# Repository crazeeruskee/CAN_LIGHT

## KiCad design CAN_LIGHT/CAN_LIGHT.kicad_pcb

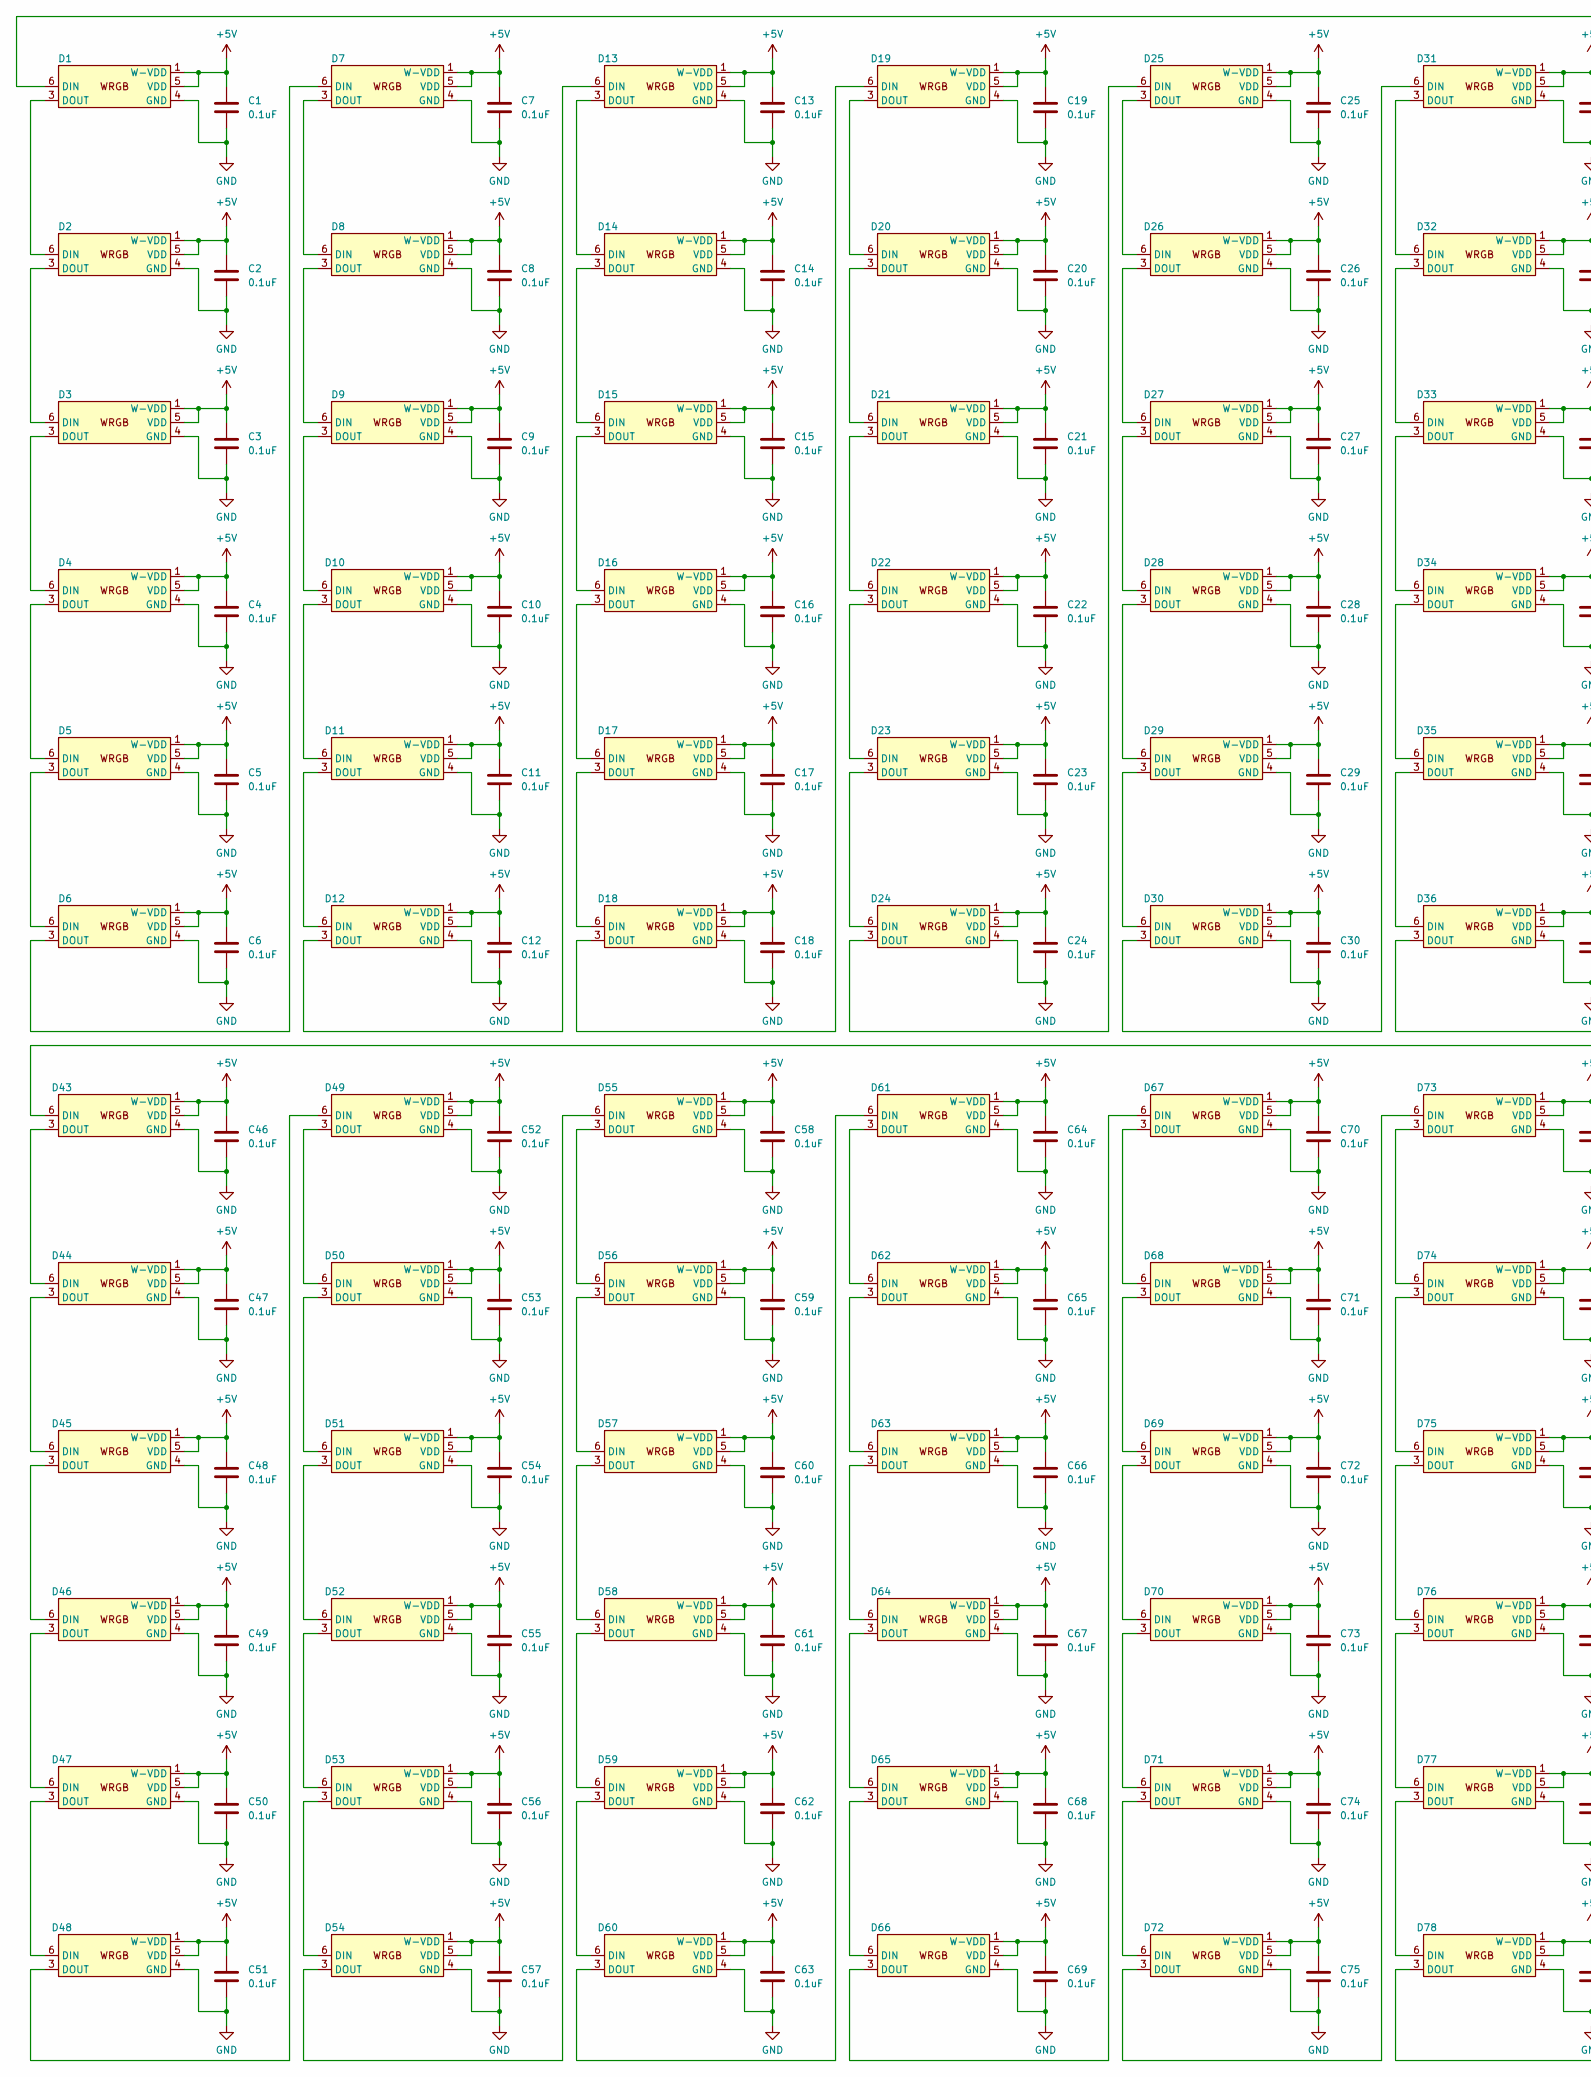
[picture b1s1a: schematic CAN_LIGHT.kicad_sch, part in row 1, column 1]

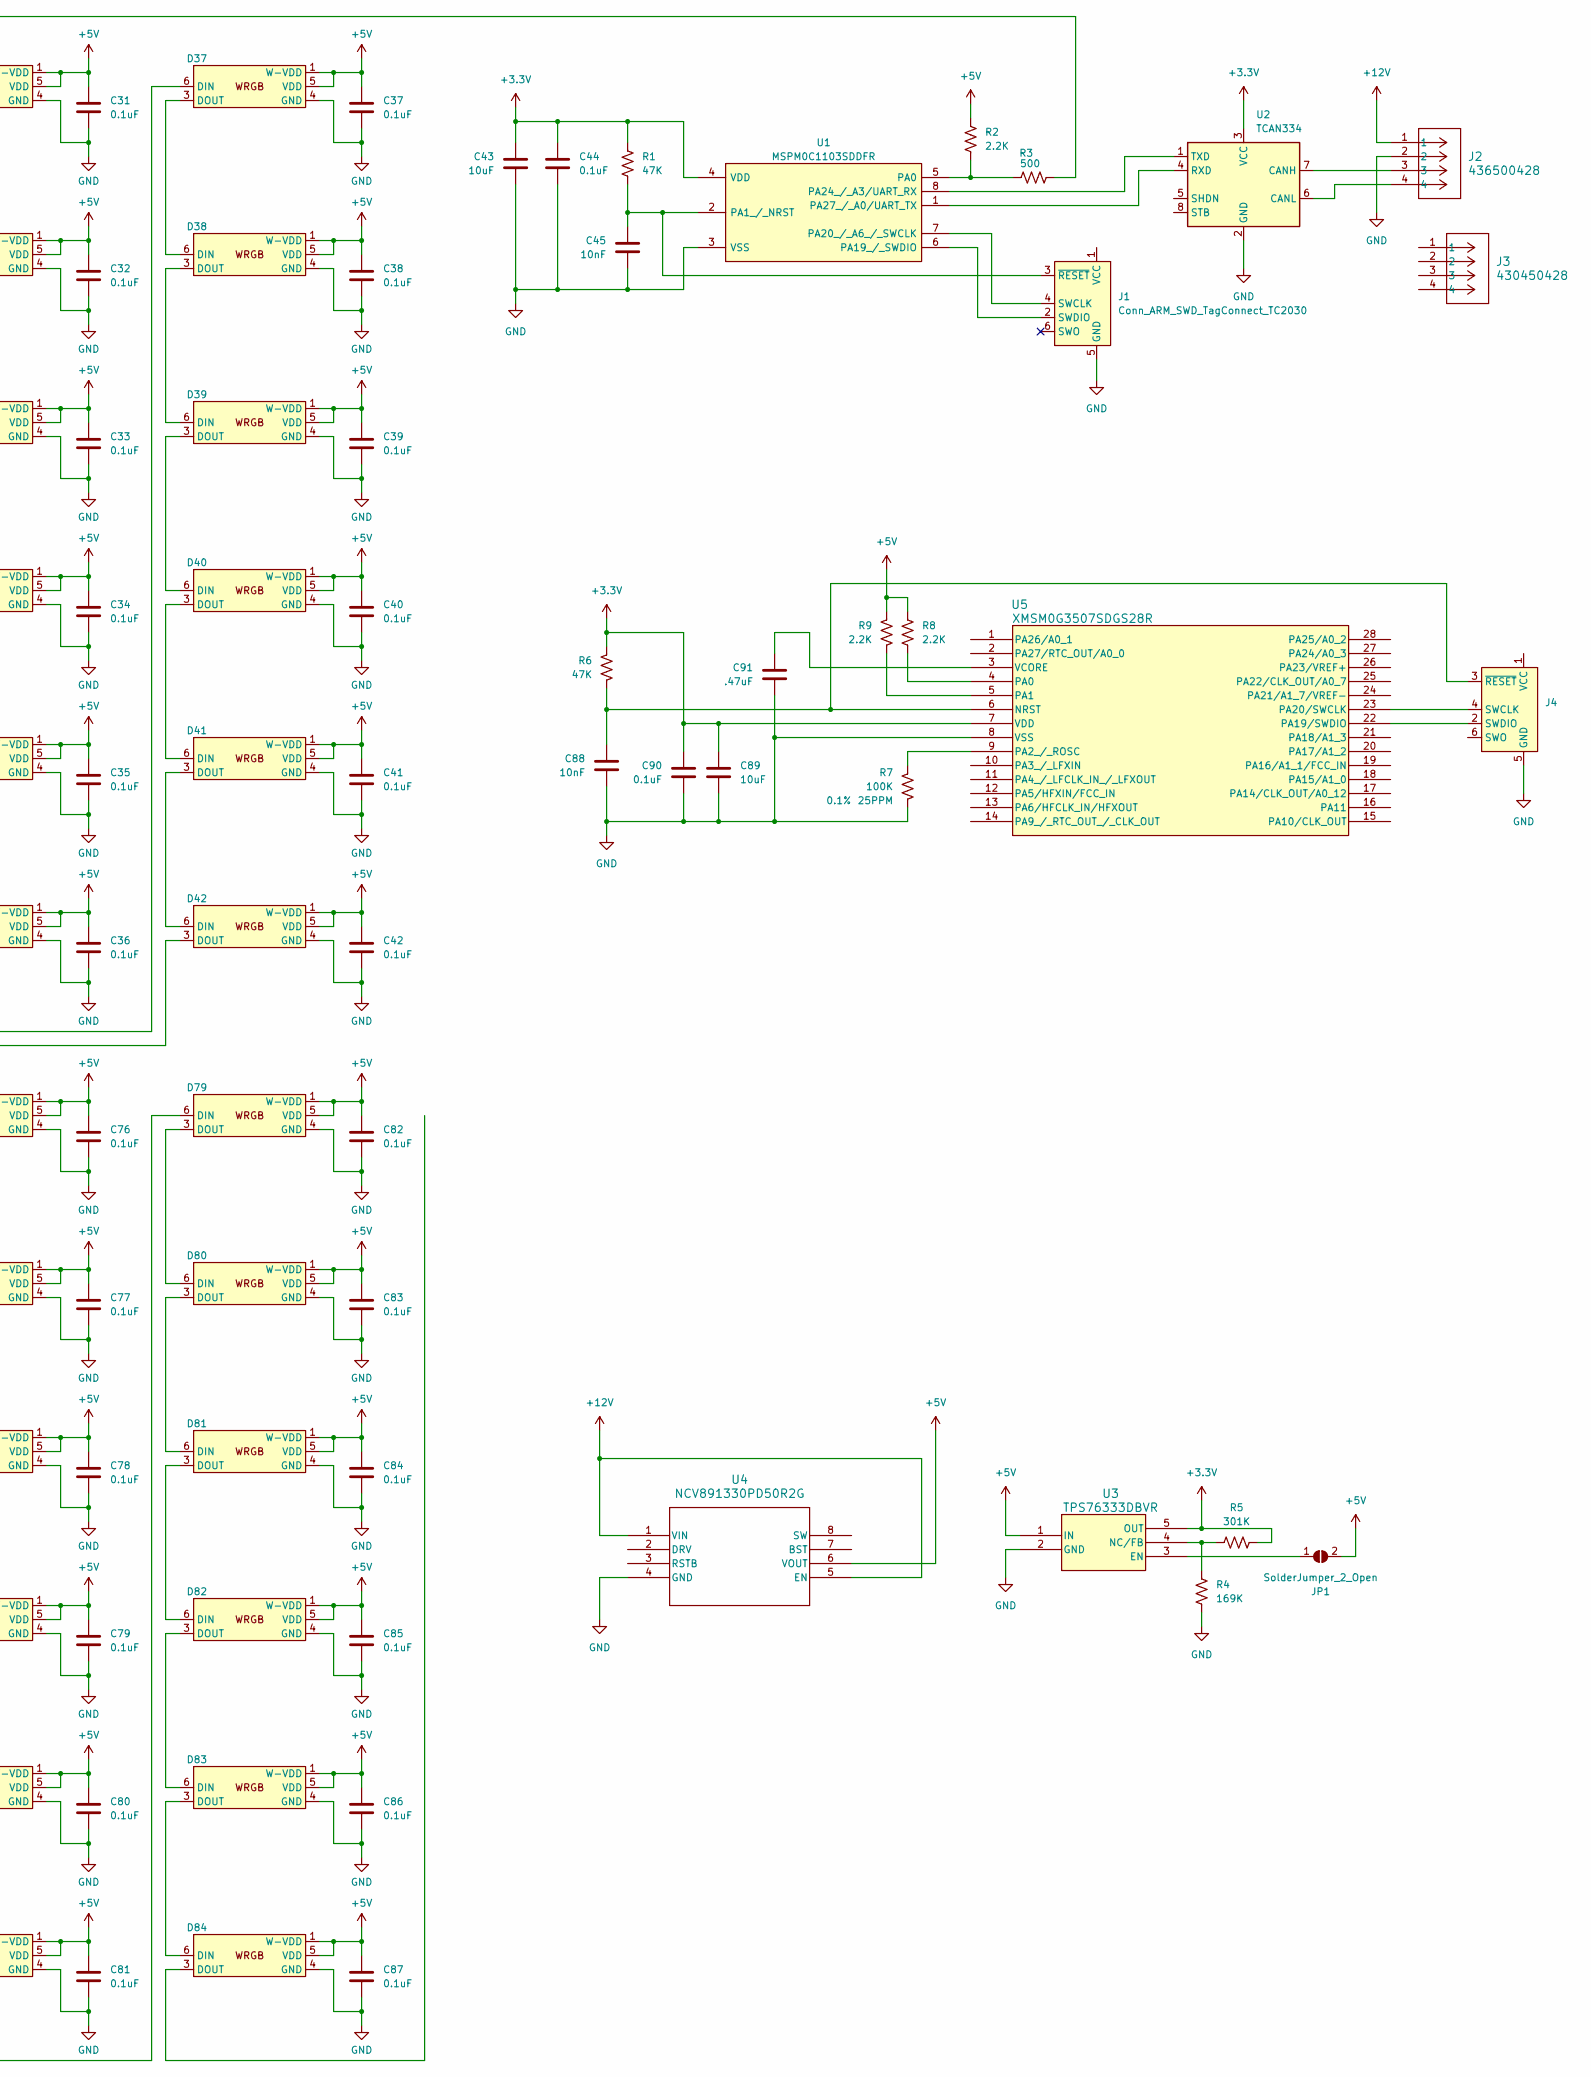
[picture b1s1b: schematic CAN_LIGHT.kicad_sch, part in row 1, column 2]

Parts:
C1, C2, C3, C4, C5, C6, C7, C8, C9, C10, C11, C12, C13, C14, C15, C16, C17, C18, C19, C20, C21, C22, C23, C24, C25, C26, C27, C28, C29, C30, C31, C32, C33, C34, C35, C36, C37, C38, C39, C40, C41, C42, C44, C46, C47, C48, C49, C50, C51, C52, C53, C54, C55, C56, C57, C58, C59, C60, C61, C62, C63, C64, C65, C66, C67, C68, C69, C70, C71, C72, C73, C74, C75, C76, C77, C78, C79, C80, C81, C82, C83, C84, C85, C86, C87, C90: 0.1uF; C_0603_1608Metric_Pad1.08x0.95mm_HandSolder
C43, C89: 10uF; C_0603_1608Metric_Pad1.08x0.95mm_HandSolder
C45, C88: 10nF; C_0603_1608Metric_Pad1.08x0.95mm_HandSolder
C91: .47uF; C_0603_1608Metric_Pad1.08x0.95mm_HandSolder
D1, D2, D3, D4, D5, D6, D7, D8, D9, D10, D11, D12, D13, D14, D15, D16, D17, D18, D19, D20, D21, D22, D23, D24, D25, D26, D27, D28, D29, D30, D31, D32, D33, D34, D35, D36, D37, D38, D39, D40, D41, D42, D43, D44, D45, D46, D47, D48, D49, D50, D51, D52, D53, D54, D55, D56, D57, D58, D59, D60, D61, D62, D63, D64, D65, D66, D67, D68, D69, D70, D71, D72, D73, D74, D75, D76, D77, D78, D79, D80, D81, D82, D83, D84: INPI4818QAS5R5G5BPW
J1: Conn_ARM_SWD_TagConnect_TC2030; Tag-Connect_TC2030-IDC-FP_2x03_P1.27mm_Vertical
J2: 436500428; CON_436500428_MOL
J3: 430450428; CON_430450428_MOL
J4: Conn_ARM_SWD_TagConnect_TC2030-NL; Tag-Connect_TC2030-IDC-NL_2x03_P1.27mm_Vertical
JP1: SolderJumper_2_Open
R1, R6: 47K; R_0603_1608Metric_Pad0.98x0.95mm_HandSolder
R2, R8, R9: 2.2K; R_0603_1608Metric_Pad0.98x0.95mm_HandSolder
R3: 500; R_0603_1608Metric_Pad0.98x0.95mm_HandSolder
R4: 169K; R_0603_1608Metric_Pad0.98x0.95mm_HandSolder
R5: 301K; R_0603_1608Metric_Pad0.98x0.95mm_HandSolder
R7: 100K; R_0603_1608Metric_Pad0.98x0.95mm_HandSolder; Tolerance 0.1%
U1: MSPM0C1103SDDFR; SOT65P280X110-8N; Manufacturer_Part_Number MSPM0C1103SDDFR
U2: TCAN334
U3: TPS76333DBVR; DBV5
U4: NCV891330PD50R2G; SOIC8_3P9X4P9_ONS
U5: XMSM0G3507SDGS28R; VSSOP28_DGS_TEX

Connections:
+3.3V: C43.1, C44.1, C89.1, C90.1, R1.1, R5.2, R6.1, U1.4 (VDD), U2.3 (VCC), U3.5 (OUT), U5.7 (VDD)
+5V: C1.1, C2.1, C3.1, C4.1, C5.1, C6.1, C7.1, C8.1, C9.1, C10.1, C11.1, C12.1, C13.1, C14.1, C15.1, C16.1, C17.1, C18.1, C19.1, C20.1, C21.1, C22.1, C23.1, C24.1, C25.1, C26.1, C27.1, C28.1, C29.1, C30.1, C31.1, C32.1, C33.1, C34.1, C35.1, C36.1, C37.1, C38.1, C39.1, C40.1, C41.1, C42.1, C46.1, C47.1, C48.1, C49.1, C50.1, C51.1, C52.1, C53.1, C54.1, C55.1, C56.1, C57.1, C58.1, C59.1, C60.1, C61.1, C62.1, C63.1, C64.1, C65.1, C66.1, C67.1, C68.1, C69.1, C70.1, C71.1, C72.1, C73.1, C74.1, C75.1, C76.1, C77.1, C78.1, C79.1, C80.1, C81.1, C82.1, C83.1, C84.1, C85.1, C86.1, C87.1, D1.1 (W-VDD), D1.5 (VDD), D2.1 (W-VDD), D2.5 (VDD), D3.1 (W-VDD), D3.5 (VDD), D4.1 (W-VDD), D4.5 (VDD), D5.1 (W-VDD), D5.5 (VDD), D6.1 (W-VDD), D6.5 (VDD), D7.1 (W-VDD), D7.5 (VDD), D8.1 (W-VDD), D8.5 (VDD), D9.1 (W-VDD), D9.5 (VDD), D10.1 (W-VDD), D10.5 (VDD), D11.1 (W-VDD), D11.5 (VDD), D12.1 (W-VDD), D12.5 (VDD), D13.1 (W-VDD), D13.5 (VDD), D14.1 (W-VDD), D14.5 (VDD), D15.1 (W-VDD), D15.5 (VDD), D16.1 (W-VDD), D16.5 (VDD), D17.1 (W-VDD), D17.5 (VDD), D18.1 (W-VDD), D18.5 (VDD), D19.1 (W-VDD), D19.5 (VDD), D20.1 (W-VDD), D20.5 (VDD), D21.1 (W-VDD), D21.5 (VDD), D22.1 (W-VDD), D22.5 (VDD), D23.1 (W-VDD), D23.5 (VDD), D24.1 (W-VDD), D24.5 (VDD), D25.1 (W-VDD), D25.5 (VDD), D26.1 (W-VDD), D26.5 (VDD), D27.1 (W-VDD), D27.5 (VDD), D28.1 (W-VDD), D28.5 (VDD), D29.1 (W-VDD), D29.5 (VDD), D30.1 (W-VDD), D30.5 (VDD), D31.1 (W-VDD), D31.5 (VDD), D32.1 (W-VDD), D32.5 (VDD), D33.1 (W-VDD), D33.5 (VDD), D34.1 (W-VDD), D34.5 (VDD), D35.1 (W-VDD), D35.5 (VDD), D36.1 (W-VDD), D36.5 (VDD), D37.1 (W-VDD), D37.5 (VDD), D38.1 (W-VDD), D38.5 (VDD), D39.1 (W-VDD), D39.5 (VDD), D40.1 (W-VDD), D40.5 (VDD), D41.1 (W-VDD), D41.5 (VDD), D42.1 (W-VDD), D42.5 (VDD), D43.1 (W-VDD), D43.5 (VDD), D44.1 (W-VDD), D44.5 (VDD), D45.1 (W-VDD), D45.5 (VDD), D46.1 (W-VDD), D46.5 (VDD), D47.1 (W-VDD), D47.5 (VDD), D48.1 (W-VDD), D48.5 (VDD), D49.1 (W-VDD), D49.5 (VDD), D50.1 (W-VDD), D50.5 (VDD), D51.1 (W-VDD), D51.5 (VDD), D52.1 (W-VDD), D52.5 (VDD), D53.1 (W-VDD), D53.5 (VDD), D54.1 (W-VDD), D54.5 (VDD), D55.1 (W-VDD), D55.5 (VDD), D56.1 (W-VDD), D56.5 (VDD), D57.1 (W-VDD), D57.5 (VDD), D58.1 (W-VDD), D58.5 (VDD), D59.1 (W-VDD), D59.5 (VDD), D60.1 (W-VDD), D60.5 (VDD), D61.1 (W-VDD), D61.5 (VDD), D62.1 (W-VDD), D62.5 (VDD), D63.1 (W-VDD), D63.5 (VDD), D64.1 (W-VDD), D64.5 (VDD), D65.1 (W-VDD), D65.5 (VDD), D66.1 (W-VDD), D66.5 (VDD), D67.1 (W-VDD), D67.5 (VDD), D68.1 (W-VDD), D68.5 (VDD), D69.1 (W-VDD), D69.5 (VDD), D70.1 (W-VDD), D70.5 (VDD), D71.1 (W-VDD), D71.5 (VDD), D72.1 (W-VDD), D72.5 (VDD), D73.1 (W-VDD), D73.5 (VDD), D74.1 (W-VDD), D74.5 (VDD), D75.1 (W-VDD), D75.5 (VDD), D76.1 (W-VDD), D76.5 (VDD), D77.1 (W-VDD), D77.5 (VDD), D78.1 (W-VDD), D78.5 (VDD), D79.1 (W-VDD), D79.5 (VDD), D80.1 (W-VDD), D80.5 (VDD), D81.1 (W-VDD), D81.5 (VDD), D82.1 (W-VDD), D82.5 (VDD), D83.1 (W-VDD), D83.5 (VDD), D84.1 (W-VDD), D84.5 (VDD), JP1.2 (B), R2.1, R8.1, R9.1, U3.1 (IN), U4.6 (VOUT)
+12V: J2.1, U4.1 (VIN), U4.5 (EN)
GND: C1.2, C2.2, C3.2, C4.2, C5.2, C6.2, C7.2, C8.2, C9.2, C10.2, C11.2, C12.2, C13.2, C14.2, C15.2, C16.2, C17.2, C18.2, C19.2, C20.2, C21.2, C22.2, C23.2, C24.2, C25.2, C26.2, C27.2, C28.2, C29.2, C30.2, C31.2, C32.2, C33.2, C34.2, C35.2, C36.2, C37.2, C38.2, C39.2, C40.2, C41.2, C42.2, C43.2, C44.2, C45.2, C46.2, C47.2, C48.2, C49.2, C50.2, C51.2, C52.2, C53.2, C54.2, C55.2, C56.2, C57.2, C58.2, C59.2, C60.2, C61.2, C62.2, C63.2, C64.2, C65.2, C66.2, C67.2, C68.2, C69.2, C70.2, C71.2, C72.2, C73.2, C74.2, C75.2, C76.2, C77.2, C78.2, C79.2, C80.2, C81.2, C82.2, C83.2, C84.2, C85.2, C86.2, C87.2, C88.2, C89.2, C90.2, C91.2, D1.4 (GND), D2.4 (GND), D3.4 (GND), D4.4 (GND), D5.4 (GND), D6.4 (GND), D7.4 (GND), D8.4 (GND), D9.4 (GND), D10.4 (GND), D11.4 (GND), D12.4 (GND), D13.4 (GND), D14.4 (GND), D15.4 (GND), D16.4 (GND), D17.4 (GND), D18.4 (GND), D19.4 (GND), D20.4 (GND), D21.4 (GND), D22.4 (GND), D23.4 (GND), D24.4 (GND), D25.4 (GND), D26.4 (GND), D27.4 (GND), D28.4 (GND), D29.4 (GND), D30.4 (GND), D31.4 (GND), D32.4 (GND), D33.4 (GND), D34.4 (GND), D35.4 (GND), D36.4 (GND), D37.4 (GND), D38.4 (GND), D39.4 (GND), D40.4 (GND), D41.4 (GND), D42.4 (GND), D43.4 (GND), D44.4 (GND), D45.4 (GND), D46.4 (GND), D47.4 (GND), D48.4 (GND), D49.4 (GND), D50.4 (GND), D51.4 (GND), D52.4 (GND), D53.4 (GND), D54.4 (GND), D55.4 (GND), D56.4 (GND), D57.4 (GND), D58.4 (GND), D59.4 (GND), D60.4 (GND), D61.4 (GND), D62.4 (GND), D63.4 (GND), D64.4 (GND), D65.4 (GND), D66.4 (GND), D67.4 (GND), D68.4 (GND), D69.4 (GND), D70.4 (GND), D71.4 (GND), D72.4 (GND), D73.4 (GND), D74.4 (GND), D75.4 (GND), D76.4 (GND), D77.4 (GND), D78.4 (GND), D79.4 (GND), D80.4 (GND), D81.4 (GND), D82.4 (GND), D83.4 (GND), D84.4 (GND), J1.5 (GND), J2.2, J4.5 (GND), R4.2, R7.2, U1.3 (VSS), U2.2 (GND), U3.2 (GND), U4.4 (GND), U5.8 (VSS)
unnamed: D1.6 (DIN), R3.2
unnamed: D1.3 (DOUT), D2.6 (DIN)
unnamed: D2.3 (DOUT), D3.6 (DIN)
unnamed: D3.3 (DOUT), D4.6 (DIN)
unnamed: D4.3 (DOUT), D5.6 (DIN)
unnamed: D5.3 (DOUT), D6.6 (DIN)
unnamed: D6.3 (DOUT), D7.6 (DIN)
unnamed: D7.3 (DOUT), D8.6 (DIN)
unnamed: D8.3 (DOUT), D9.6 (DIN)
unnamed: D9.3 (DOUT), D10.6 (DIN)
unnamed: D10.3 (DOUT), D11.6 (DIN)
unnamed: D11.3 (DOUT), D12.6 (DIN)
unnamed: D12.3 (DOUT), D13.6 (DIN)
unnamed: D13.3 (DOUT), D14.6 (DIN)
unnamed: D14.3 (DOUT), D15.6 (DIN)
unnamed: D15.3 (DOUT), D16.6 (DIN)
unnamed: D16.3 (DOUT), D17.6 (DIN)
unnamed: D17.3 (DOUT), D18.6 (DIN)
unnamed: D18.3 (DOUT), D19.6 (DIN)
unnamed: D19.3 (DOUT), D20.6 (DIN)
unnamed: D20.3 (DOUT), D21.6 (DIN)
unnamed: D21.3 (DOUT), D22.6 (DIN)
unnamed: D22.3 (DOUT), D23.6 (DIN)
unnamed: D23.3 (DOUT), D24.6 (DIN)
unnamed: D24.3 (DOUT), D25.6 (DIN)
unnamed: D25.3 (DOUT), D26.6 (DIN)
unnamed: D26.3 (DOUT), D27.6 (DIN)
unnamed: D27.3 (DOUT), D28.6 (DIN)
unnamed: D28.3 (DOUT), D29.6 (DIN)
unnamed: D29.3 (DOUT), D30.6 (DIN)
unnamed: D30.3 (DOUT), D31.6 (DIN)
unnamed: D31.3 (DOUT), D32.6 (DIN)
unnamed: D32.3 (DOUT), D33.6 (DIN)
unnamed: D33.3 (DOUT), D34.6 (DIN)
unnamed: D34.3 (DOUT), D35.6 (DIN)
unnamed: D35.3 (DOUT), D36.6 (DIN)
unnamed: D36.3 (DOUT), D37.6 (DIN)
unnamed: D37.3 (DOUT), D38.6 (DIN)
unnamed: D38.3 (DOUT), D39.6 (DIN)
unnamed: D39.3 (DOUT), D40.6 (DIN)
unnamed: D40.3 (DOUT), D41.6 (DIN)
unnamed: D41.3 (DOUT), D42.6 (DIN)
unnamed: D42.3 (DOUT), D43.6 (DIN)
unnamed: D43.3 (DOUT), D44.6 (DIN)
unnamed: D44.3 (DOUT), D45.6 (DIN)
unnamed: D45.3 (DOUT), D46.6 (DIN)
unnamed: D46.3 (DOUT), D47.6 (DIN)
unnamed: D47.3 (DOUT), D48.6 (DIN)
unnamed: D48.3 (DOUT), D49.6 (DIN)
unnamed: D49.3 (DOUT), D50.6 (DIN)
unnamed: D50.3 (DOUT), D51.6 (DIN)
unnamed: D51.3 (DOUT), D52.6 (DIN)
unnamed: D52.3 (DOUT), D53.6 (DIN)
unnamed: D53.3 (DOUT), D54.6 (DIN)
unnamed: D54.3 (DOUT), D55.6 (DIN)
unnamed: D55.3 (DOUT), D56.6 (DIN)
unnamed: D56.3 (DOUT), D57.6 (DIN)
unnamed: D57.3 (DOUT), D58.6 (DIN)
unnamed: D58.3 (DOUT), D59.6 (DIN)
unnamed: D59.3 (DOUT), D60.6 (DIN)
unnamed: D60.3 (DOUT), D61.6 (DIN)
unnamed: D61.3 (DOUT), D62.6 (DIN)
unnamed: D62.3 (DOUT), D63.6 (DIN)
unnamed: D63.3 (DOUT), D64.6 (DIN)
unnamed: D64.3 (DOUT), D65.6 (DIN)
unnamed: D65.3 (DOUT), D66.6 (DIN)
unnamed: D66.3 (DOUT), D67.6 (DIN)
unnamed: D67.3 (DOUT), D68.6 (DIN)
unnamed: D68.3 (DOUT), D69.6 (DIN)
unnamed: D69.3 (DOUT), D70.6 (DIN)
unnamed: D70.3 (DOUT), D71.6 (DIN)
unnamed: D71.3 (DOUT), D72.6 (DIN)
unnamed: D72.3 (DOUT), D73.6 (DIN)
unnamed: D73.3 (DOUT), D74.6 (DIN)
unnamed: D74.3 (DOUT), D75.6 (DIN)
unnamed: D75.3 (DOUT), D76.6 (DIN)
unnamed: D76.3 (DOUT), D77.6 (DIN)
unnamed: D77.3 (DOUT), D78.6 (DIN)
unnamed: D78.3 (DOUT), D79.6 (DIN)
unnamed: D79.3 (DOUT), D80.6 (DIN)
unnamed: D80.3 (DOUT), D81.6 (DIN)
unnamed: D81.3 (DOUT), D82.6 (DIN)
unnamed: D82.3 (DOUT), D83.6 (DIN)
unnamed: D83.3 (DOUT), D84.6 (DIN)
unnamed: J1.4 (SWCLK), U1.7 (PA20_/_A6_/_SWCLK)
unnamed: J1.2 (SWDIO), U1.6 (PA19_/_SWDIO)
unnamed: C45.1, J1.3 (~RESET), R1.2, U1.2 (PA1_/_NRST)
unnamed: J4.4 (SWCLK), U5.23 (PA20/SWCLK)
unnamed: J4.2 (SWDIO), U5.22 (PA19/SWDIO)
unnamed: C88.1, J4.3 (~RESET), R6.2, U5.6 (NRST)
unnamed: JP1.1 (A), U3.3 (EN)
unnamed: R2.2, R3.1, U1.5 (PA0)
unnamed: U1.8 (PA24_/_A3/UART_RX), U2.1 (TXD)
unnamed: U1.1 (PA27_/_A0/UART_TX), U2.4 (RXD)
unnamed: J2.3, U2.7 (CANH)
unnamed: J2.4, U2.6 (CANL)
unnamed: R4.1, R5.1, U3.4 (NC/FB)
unnamed: R8.2, U5.4 (PA0)
unnamed: R9.2, U5.5 (PA1)
unnamed: R7.1, U5.9 (PA2_/_ROSC)
unnamed: C91.1, U5.3 (VCORE)

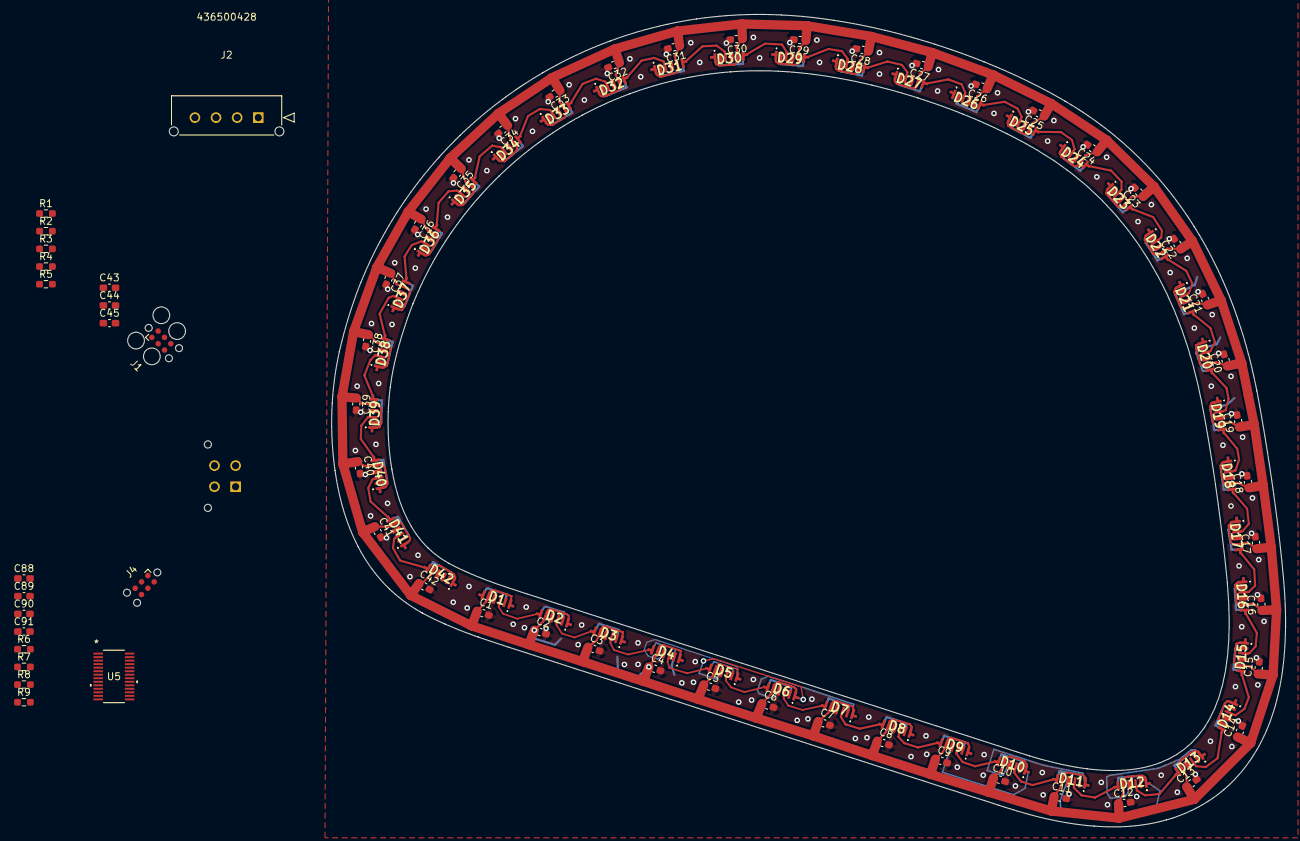
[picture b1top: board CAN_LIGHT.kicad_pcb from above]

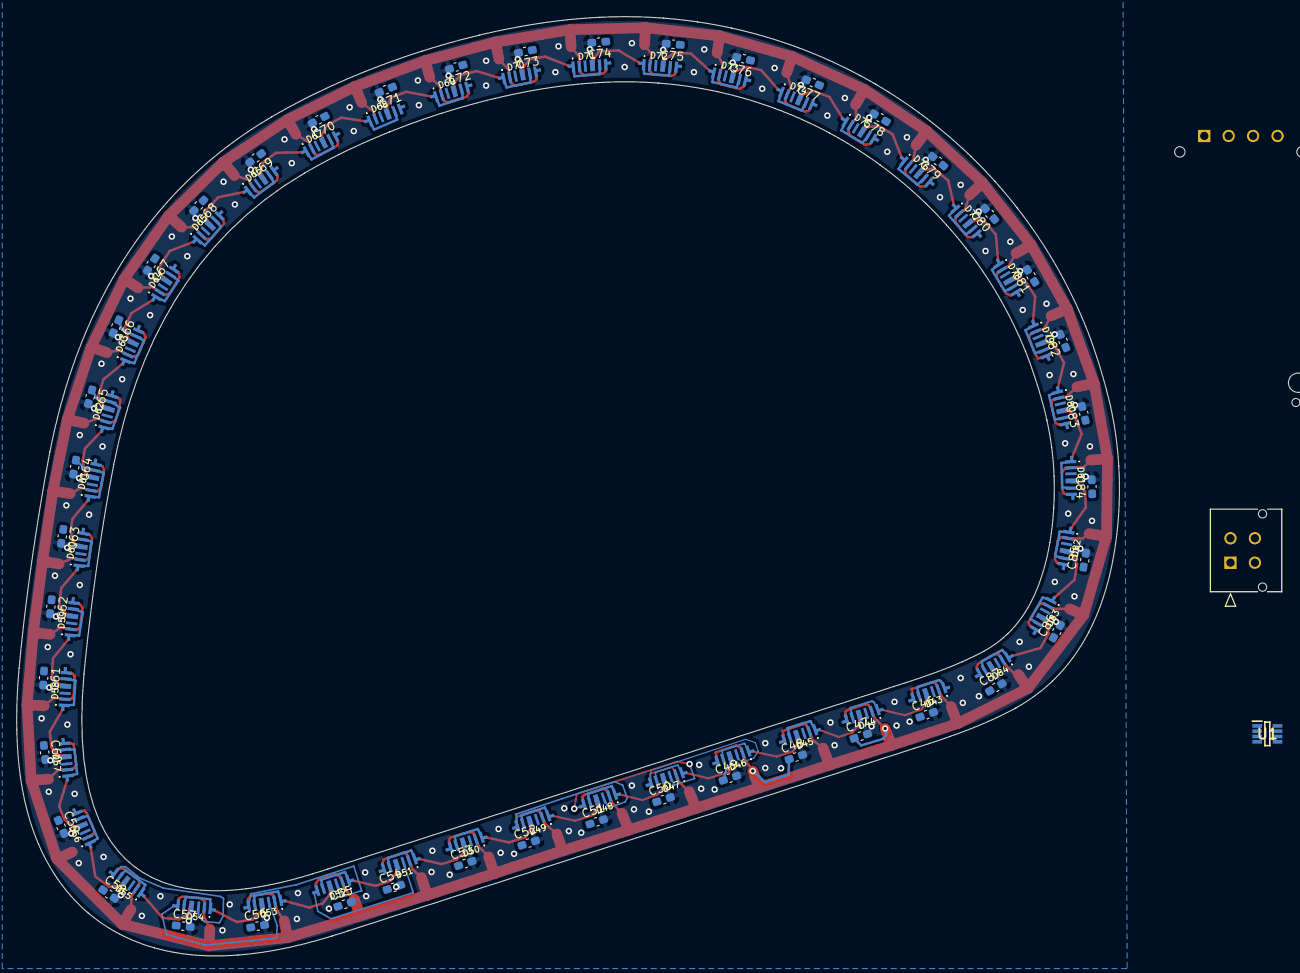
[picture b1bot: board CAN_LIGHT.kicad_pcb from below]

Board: 2 copper layers, 135.5 x 115.4 mm, 190 parts (86 on the bottom side), 99 nets.

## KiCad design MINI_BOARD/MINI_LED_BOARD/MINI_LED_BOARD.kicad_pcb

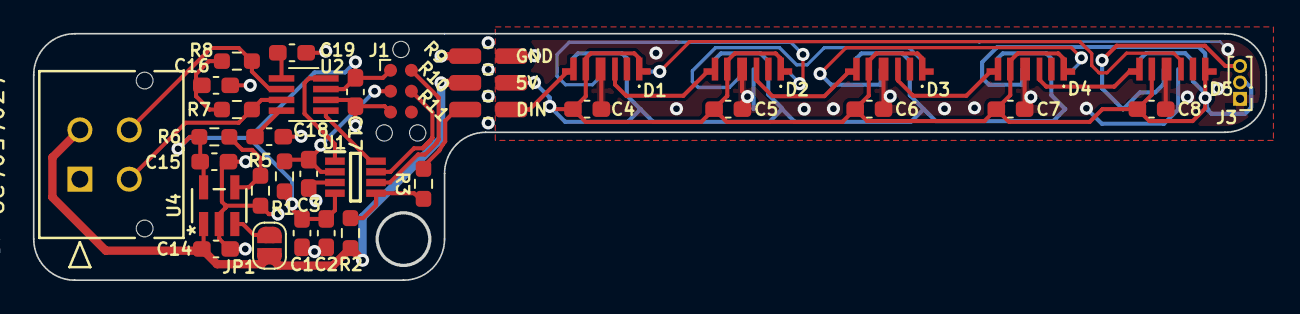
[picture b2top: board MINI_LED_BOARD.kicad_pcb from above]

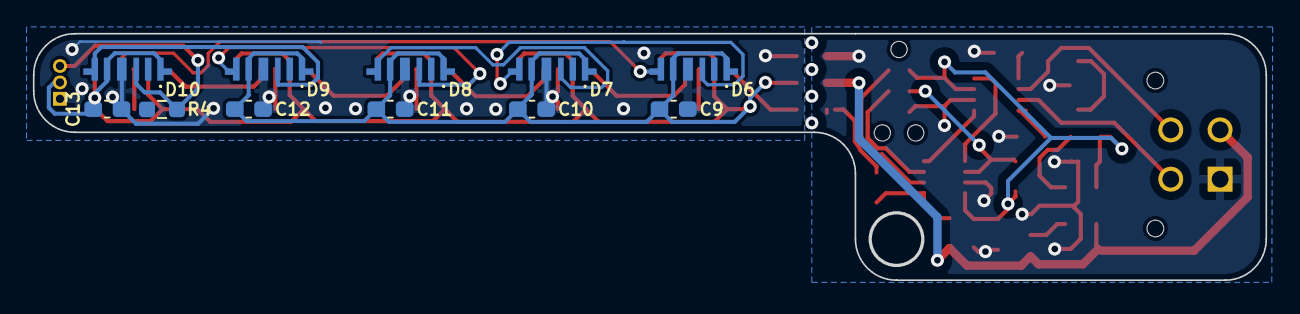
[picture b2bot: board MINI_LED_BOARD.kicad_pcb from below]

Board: 2 copper layers, 75.0 x 15.0 mm, 47 parts (11 on the bottom side), 30 nets.

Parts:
C1: 10uF; C_0603_1608Metric_Pad1.08x0.95mm_HandSolder
C2: 0.1uF; C_0603_1608Metric_Pad1.08x0.95mm_HandSolder
C3: 10nF; C_0603_1608Metric_Pad1.08x0.95mm_HandSolder
C4, C5, C6, C7, C8, C9, C10, C11, C12, C13, C14, C16, C17, C18, C19: 1uF; C_0603_1608Metric_Pad1.08x0.95mm_HandSolder
C15: 4.7uF; C_0603_1608Metric_Pad1.08x0.95mm_HandSolder
D1, D2, D3, D4, D5, D6, D7, D8, D9, D10: INPI4818QAS5R5G5BPW
J1: Conn_ARM_SWD_TagConnect_TC2030-NL; Tag-Connect_TC2030-IDC-NL_2x03_P1.27mm_Vertical
J2: 430450428; CON_430450428_MOL
J3: Conn_01x03_Socket; PinHeader_1x03_P1.00mm_Vertical
JP1: SolderJumper_2_Open; SolderJumper-2_P1.3mm_Open_RoundedPad1.0x1.5mm
R1: 47K; R_0603_1608Metric_Pad0.98x0.95mm_HandSolder
R2: 2.2K; R_0603_1608Metric_Pad0.98x0.95mm_HandSolder
R3, R4: 500; R_0603_1608Metric_Pad0.98x0.95mm_HandSolder
R5: 169K; R_0603_1608Metric_Pad0.98x0.95mm_HandSolder
R6: 301K; R_0603_1608Metric_Pad0.98x0.95mm_HandSolder
R7, R8: 60; R_0603_1608Metric_Pad0.98x0.95mm_HandSolder
R9, R10, R11: 0; R_0603_1608Metric_Pad0.98x0.95mm_HandSolder
U1: MSPM0C1103SDDFR; SOT65P280X110-8N
U2: TCAN334; SOT-23-8_Handsoldering
U4: TPS76333DBVR; DBV5

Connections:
+3.3V: C1.1, C2.1, C15.1, C17.2, J1.1 (VCC), R1.1, R6.2, U1.4 (VDD), U2.3 (VCC), U4.5 (OUT)
+5V: C14.1, J2.2, JP1.2 (B), R2.1, R10.1, U4.1 (IN)
GND: C1.2, C2.2, C3.2, C14.2, C15.2, C16.2, C17.1, C18.2, C19.2, J1.5 (GND), J2.1, R5.2, R9.2, U1.3 (VSS), U2.2 (GND), U4.2 (GND)
GND2: C4.2, C5.2, C6.2, C7.2, C8.2, C9.2, C10.2, C11.2, C12.2, C13.2, D1.4 (GND), D2.4 (GND), D3.4 (GND), D4.4 (GND), D5.4 (GND), D6.4 (GND), D7.4 (GND), D8.4 (GND), D9.4 (GND), D10.4 (GND), J3.1, R9.1
unnamed: C16.1, R7.1, R8.2
unnamed: D1.6 (DIN), R11.1
unnamed: D1.3 (DOUT), D2.6 (DIN)
unnamed: D2.3 (DOUT), D3.6 (DIN)
unnamed: D3.3 (DOUT), D4.6 (DIN)
unnamed: D4.3 (DOUT), D5.6 (DIN)
unnamed: D5.3 (DOUT), D6.6 (DIN)
unnamed: D6.3 (DOUT), D7.6 (DIN)
unnamed: D7.3 (DOUT), D8.6 (DIN)
unnamed: D8.3 (DOUT), D9.6 (DIN)
unnamed: D9.3 (DOUT), D10.6 (DIN)
unnamed: D10.3 (DOUT), J3.3, R4.1
unnamed: J1.4 (SWCLK), U1.7 (PA20_/_A6_/_SWCLK)
unnamed: J1.2 (SWDIO), U1.6 (PA19_/_SWDIO)
unnamed: C3.1, J1.3 (~RESET), R1.2, U1.2 (PA1_/_NRST)
unnamed: JP1.1 (A), U4.3 (EN)
unnamed: R3.2, R11.2
unnamed: R2.2, R3.1, U1.5 (PA0)
unnamed: U1.8 (PA24_/_A3/UART_RX), U2.1 (TXD)
unnamed: U1.1 (PA27_/_A0/UART_TX), U2.4 (RXD)
unnamed: J2.3, R7.2, U2.7 (CANH)
unnamed: J2.4, R8.1, U2.6 (CANL)
unnamed: C19.1, U2.5 (SHDN)
unnamed: C18.1, U2.8 (STB)
unnamed: R5.1, R6.1, U4.4 (NC/FB)
VDD: C4.1, C5.1, C6.1, C7.1, C8.1, C9.1, C10.1, C11.1, C12.1, C13.1, D1.1 (W-VDD), D1.5 (VDD), D2.1 (W-VDD), D2.5 (VDD), D3.1 (W-VDD), D3.5 (VDD), D4.1 (W-VDD), D4.5 (VDD), D5.1 (W-VDD), D5.5 (VDD), D6.1 (W-VDD), D6.5 (VDD), D7.1 (W-VDD), D7.5 (VDD), D8.1 (W-VDD), D8.5 (VDD), D9.1 (W-VDD), D9.5 (VDD), D10.1 (W-VDD), D10.5 (VDD), J3.2, R10.2

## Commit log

2024-07-19 Add level shifter
2024-07-20 Add custom WRGB symbol
2024-08-19 Select and implement MCU; Add TagConnect port
2024-08-20 Wire up LEDs, MCU, CAN transceiver, and input port
2024-08-20 Add 5V to 3V3 LDO
2024-08-21 Wire LEDs to MCU
2024-08-22 Add 12V to 5V buck converter
2024-08-23 Import initial PCB shape and roughly place LEDs on perimeter
2024-08-24 Shift layout slightly
2024-08-24 Move LEDs to outside of curve, add 5 more to fill out outline
2024-08-26 Fix 3D bodies
2024-08-27 Place more LEDs and experiment with routing paths
2024-08-28 Place more LEDs
2024-08-29 Finish LED placements
2024-08-30 Place caps
2024-08-31 Mess with routing
2024-09-01 Route several LEDs
2024-09-02 Route a large portion of the board
2024-09-02 Finish top layer LED routing
2024-09-03 Export initial STEP file to print
2024-09-04 Add back side LEDs
2024-09-04 Roughly place backside LEDs
2024-09-05 Set backside LEDs in place
2024-09-05 Roughly place caps; output updated PCB STEP file
2024-09-06 Select new MCU with CAN controller peripheral included
2024-09-07 Add passives to MCU
2024-09-09 Create mini version of can_light board
2024-09-09 Update LED routing
2024-09-10 Start laying out components
2024-09-10 Complete more major layout placement
2024-09-11 Add more footprints and adjust layout placements
2024-09-12 Add more TCAN passives and mess with layout
2024-09-13 Create initial rough board edge
2024-09-14 Refine board shape and layout
2024-09-15 Finalize layout and conenction features; begin routing
2024-09-15 Fix 3D models on components and re-export step file
2024-09-16 Complete MCU side routing
2024-09-17 Route LED side
2024-09-18 Fix mcu side routing and update mcu-led jumper resistor pads
2024-09-19 More LED side routing changes
2024-09-20 Clean up silkscreen; route more LED side signals
2024-09-22 Route last LED signals, still need to fix GND connections
2024-09-23 Fix LED GND connection
2024-09-24 Enlarge LED 5V track, adjust routing accordingly
2024-09-25 Create first pass JTAG clamp tool
2024-09-27 Adjut JTAG clamp tagconnect spacing
2024-09-29 Mionr routing
2024-09-30 Route top level 5V
2024-10-01 Route some of bottom level 5V
2024-10-02 Route some more bottom level 5V
2024-10-03 Route bottom level 5V LED traces and GND vias
2024-10-04 Route bottom 5V to larger rail
2024-10-05 Investigate routing strategy on bottom LED signals
2024-10-09 Mess with routing strategy
2024-11-12 Adjust IC footprint pads to clear soldermask bridge requirements
